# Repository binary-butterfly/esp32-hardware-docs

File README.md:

# Universelle ESP32 Steuerungs-Platine 

Die ESP32 Steuerungs-Platine wurde als Hardware zum MicroPython-basierten [Open Booking Client](https://github.com/binary-butterfly/open-booking-client-esp32) entwickelt. Sie eignet sich aber für eine ganze Reihe anderer Anwendungen.

# Urheberschaft / Lizenz

Das Platinenlayout wurde von der [TUG Herrenberg](https://tug-herrenberg.de) entwickelt, Dokumentation und Software stammen von der [binary butterfly GmbH](https://binary-butterfly.de). Die Platine wurde im Rahmen des Förderprojektes [stadtnavi](https://stadtnavi.de) entwickelt.

Alle Daten im Repository stehen unter der [Creative Commons BY](https://creativecommons.org/licenses/by/4.0/).

# Dokumentation

* [Setup](./docs/setup.md)
* [Materialliste](./docs/hardware.md)
* [Board-Herstellung](./docs/production.md)

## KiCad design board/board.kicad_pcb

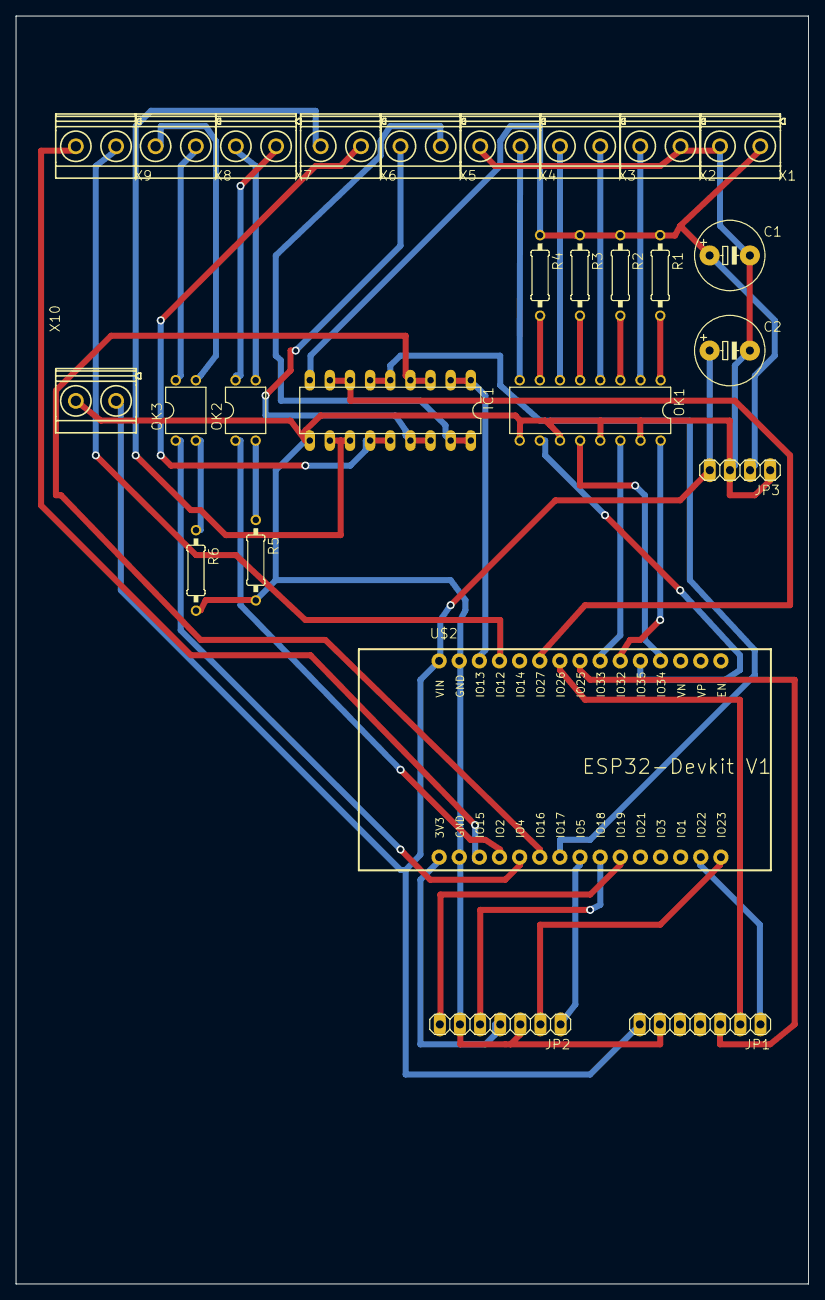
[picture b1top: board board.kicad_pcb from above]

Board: 2 copper layers, 100.0 x 160.0 mm, 26 parts (0 on the bottom side), 41 nets.

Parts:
C1, C2: CPOL-EUE5-8.5; E5-8,5
IC1: UDN298A; DIL18
JP1, JP2: PINHD-1X7; 1X07
JP3: PINHD-1X4; 1X04
OK1: PC847; DIL16
OK2, OK3: PC817; DIL04
R1, R2, R3, R4, R5, R6: R-EU_0207_10; 0207_10
U$2: ESP32-DEVKITV1_ESP32DEVKITV1; ESP32-DEVKITV1_ESP32-DEVKITV1
X1, X2, X3, X4, X5, X6, X7, X8, X9, X10: MKDSN1,5_2-5,08

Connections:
/2: OK2.1, U$2.4
/3V: JP2.4, U$2.1
/4: OK3.1, U$2.5
/5V: C2.+, JP1.7, JP3.4, U$2.30, X10.1
/12V: C1.+, IC1.9, JP3.2, R1.1, R2.1, R3.1, R4.1, X1.1
/13: IC1.1, IC1.2, U$2.28
/16: IC1.3, IC1.4, U$2.6
/17: IC1.5, IC1.6, U$2.7
/27: IC1.7, IC1.8, U$2.25
/32: OK1.16, U$2.21
/33: OK1.14, U$2.22
/34: OK1.12, U$2.19
/35: OK1.10, U$2.20
/BCLK: JP1.2, U$2.24
/DIN: JP1.3, U$2.23
/GND: C1.-, C2.-, IC1.10, JP1.6, JP2.3, JP2.6, JP3.1, JP3.3, OK1.9, OK1.11, OK1.13, OK1.15, R5.2, R6.2, U$2.2, U$2.29, X1.2, X2.1, X4.2, X10.2
/LRC: JP1.1, U$2.14
/MISO: JP2.7, U$2.10
/MOSI: JP2.2, U$2.15
/RXD3: U$2.3, X9.2
/SCK: JP2.5, U$2.9
/SS: JP2.1, U$2.8
/TXD3: U$2.27, X9.1
unnamed: IC1.11, IC1.12, X6.2
unnamed: IC1.13, IC1.14, X6.1
unnamed: IC1.15, IC1.16, X5.2
unnamed: IC1.17, IC1.18, X5.1
unnamed: OK1.1, R1.2
unnamed: OK1.2, X2.2
unnamed: OK1.3, R2.2
unnamed: OK1.4, X3.1
unnamed: OK1.5, R3.2
unnamed: OK1.6, X3.2
unnamed: OK1.7, R4.2
unnamed: OK1.8, X4.1
unnamed: OK2.2, R5.1
unnamed: OK2.3, X7.2
unnamed: OK2.4, X7.1
unnamed: OK3.2, R6.1
unnamed: OK3.3, X8.2
unnamed: OK3.4, X8.1

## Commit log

2021-06-23 init
2021-06-24 licence
2021-06-24 stadtnavi name fix
